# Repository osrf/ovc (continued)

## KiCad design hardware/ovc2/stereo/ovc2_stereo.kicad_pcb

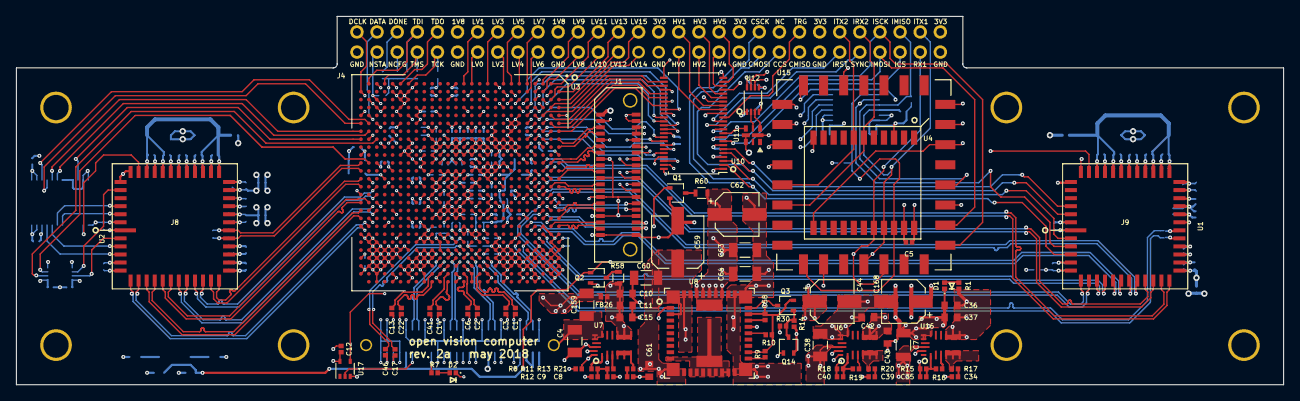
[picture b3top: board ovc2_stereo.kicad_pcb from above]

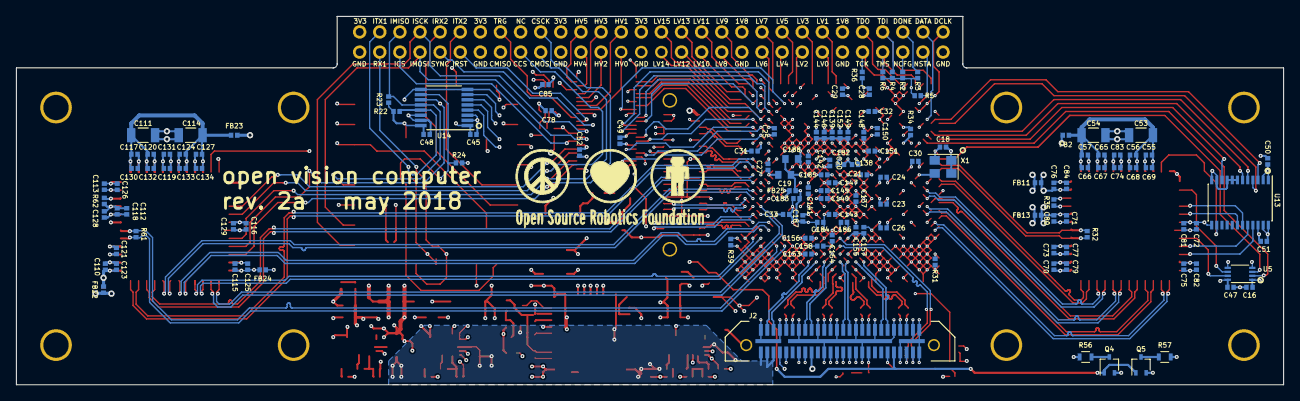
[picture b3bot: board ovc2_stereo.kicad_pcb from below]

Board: 6 copper layers, 160.0 x 46.5 mm, 217 parts (135 on the bottom side), 222 nets.

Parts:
C1, C2, C3, C5, C6, C12, C13, C14, C16, C17, C22, C27, C28, C41, C45, C46, C47, C48, C49, C50, C51, C52, C77, C78, C79, C80, C81, C82, C83, C84, C85, C121, C123, C125, C126, C128, C129, C131, C146, C147, C154, C155, C183, C184: 100n; C_0402_1005Metric
C4, C7, C38, C60: 22u; C_1206_3216Metric
C8, C34, C39: 470p; C_0402_1005Metric
C9, C35, C40: 22p; C_0402_1005Metric
C10, C11, C15, C36, C37, C42, C43: 22u; C_0603_1608Metric
C18, C75, C118, C143: 10n; C_0402_1005Metric
C19, C188: 47u; C_0603_1608Metric
C20, C21, C23, C24, C137, C138, C139, C140, C141, C142, C153, C182: 22n; C_0402_1005Metric
C25, C26, C144, C145: 47n; C_0402_1005Metric
C29, C148, C156, C185: 220n; C_0402_1005Metric
C30, C149, C157, C186: 470n; C_0402_1005Metric
C31, C66, C67, C68, C69, C130, C132, C133, C134, C150, C158, C187: 1u; C_0402_1005Metric
C32, C33, C55, C56, C57, C65, C74, C76, C116, C117, C119, C120, C124, C127, C151, C152: 4u7; C_0402_1005Metric
C44, C62, C168: 220u; CP_Elec_5x5.9
C53, C54, C63, C64, C111, C114, C159: 100u; C_1206_3216Metric
C58: 3n3; C_0402_1005Metric
C59: 100u; CP_Elec_6.3x7.7
C61: 100n; C_0603_1608Metric
C70, C71, C72, C73, C110, C112, C113, C115: 10u; C_0402_1005Metric
D1: LED_Red; LED_0402_1005Metric
D2: LED_Green; LED_0402_1005Metric
FB2, FB11, FB13, FB22, FB23, FB24, FB25, FB26: 60; R_0402_1005Metric
J1: HIGH-SPEED EXPANSION; SAMTEC_ERF8-020
J2: Samtec QRM8; SAMTEC_QRM8-026-02.0-L-D-A-GP
J4: LOW-SPEED EXPANSION; Pin_Header_Straight_2x30_Pitch2.54mm
J8, J9: LENS_HOLDER; LENS_HOLDER_30MM
Q1, Q2, Q3, Q4, Q5, Q14: NTS4001NT1G; SOT-323_SC-70
R1, R7: 330; R_0402_1005Metric
R2, R3, R4, R5, R6, R8, R14, R22, R23, R24, R30: 10k; R_0402_1005Metric
R9: 1M; R_0402_1005Metric
R10: 2k87; R_0402_1005Metric
R11, R12, R15, R18: 51k; R_0402_1005Metric
R13: 71k5; R_0402_1005Metric
R16: 11k3; R_0402_1005Metric
R17, R20, R21: 5R1; R_0402_1005Metric
R19: 25k5; R_0402_1005Metric
R31, R39: 2k; R_0402_1005Metric
R32, R61: 100; R_0402_1005Metric
R34, R36: 1k; R_0402_1005Metric
R35, R62: 47k; R_0402_1005Metric
R56, R57, R58, R60: 47; R_0603
U1, U2: NOIP1SN1300A-QDI; LCC101.6P1422X1422X165-48
U3: 10CXyyy_F672; INTEL_F672
U4: VN-100
U5, U12: SN74LVC2T45; VSSOP-8_2.3x2mm_Pitch0.5mm
U6, U7, U16: MPM3630
U8: LMZ31707; TI_RVQ_42
U10: SN74AVC16T245; TSSOP-48_6.1x12.5mm_Pitch0.5mm
U11: led_dotstar_micro; APA102_2020
U13: SN74AVC8T245; TSSOP-24_4.4x7.8mm_Pitch0.65mm
U14: SN74AVC4T245; TSSOP-16_4.4x5mm_Pitch0.65mm
U15: uIMU-2; DFP-22_0.5mmPitch_125x155mm
U17: 74LVC1G34; SOT-353_SC-70-5
X1: ASEMB-100MHz; Oscillator_SMD_Abracon_ASE-4pin_3.2x2.5mm
Z1: Logo_Open_Hardware_Small; OSHW-Symbol_6.7x6mm_SilkScreen
Z2: Logo_Open_Hardware_Small; OSRF_logo

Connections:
0V9: C62.1, C63.1, C64.1, C137.1, C138.1, C139.1, C140.1, C141.1, C142.1, C143.1, C144.1, C145.1, C146.1, C147.1, C148.1, C149.1, C150.1, C151.1, C152.1, R60.1, U3.K9, U3.K10, U3.K15, U3.K16, U3.K17, U3.L8, U3.L9, U3.L13, U3.L14, U3.L17, U3.L18, U3.M8, U3.M9, U3.M10, U3.M13, U3.M14, U3.M15, U3.M16, U3.N8, U3.N10, U3.N12, U3.N15, U3.N16, U3.N17, U3.N18, U3.P8, U3.P9, U3.P10, U3.P12, U3.P13, U3.P14, U3.P15, U3.P17, U3.P18, U3.R9, U3.R12, U3.R14, U3.R15, U3.R16, U3.R17, U3.T8, U3.T9, U3.T12, U3.T13, U3.T14, U3.T17, U3.T18, U3.U8, U3.U9, U3.U10, U3.U11, U3.U13, U3.U14, U3.U15, U3.U16, U3.U18, U8.27, U8.34, U8.35, U8.36, U8.37, U8.38, U8.41
1V03: C9.1, C10.1, C11.1, C15.1, FB26.2, R12.1, R58.1, U7.7, U7.8, U7.9
+1V8: C12.1, C16.1, C18.1, C20.1, C21.1, C23.1, C24.1, C25.1, C26.1, C27.1, C28.1, C29.1, C30.1, C31.1, C32.1, C33.1, C40.1, C42.1, C43.1, C44.1, C45.1, C49.1, C50.1, C85.1, FB13.2, FB24.2, FB25.2, J1.6, J1.8, J4.12, J4.22, R2.1, R3.1, R4.1, R5.1, R6.1, R18.1, R34.1, R57.1, U3.AA15, U3.AB12, U3.AB17, U3.C9, U3.D11, U3.D16, U3.E8, U3.E18, U3.F15, U3.L11, U3.L16, U3.R3, U3.T5, U3.T11, U3.T16, U3.U2, U3.V10, U3.V11, U3.V12, U3.W16, U3.Y13, U3.Y18, U5.1, U6.7, U6.8, U6.9, U10.1, U10.24, U10.31, U10.42, U12.8, U13.1, U13.2, U14.1, U17.5, X1.1, X1.4
+3V3: C5.1, C35.1, C36.1, C37.1, C47.1, C48.1, C51.1, C52.1, C168.1, FB2.2, FB11.2, FB22.2, FB23.2, J1.2, J1.4, J4.32, J4.40, J4.48, J4.60, R1.2, R15.1, R22.1, R23.1, R24.1, R56.1, U4.10, U5.8, U10.7, U10.18, U13.23, U13.24, U14.16, U15.3, U15.22, U16.7, U16.8, U16.9
+5V: C78.1, J1.1, J2.18, U11.1, U12.1
+12V: C4.1, C7.1, C38.1, C59.1, C60.1, C61.1, J2.2, J2.4, J2.6, R30.1, U6.16, U7.16, U8.1, U8.3, U8.11, U8.12, U8.39, U8.40, U16.16
/fpga_io/CAM1_CS_1V8: U3.D7, U10.44
/fpga_io/CAM1_MISO_1V8: U3.G3, U14.6
/fpga_io/CAM1_MOSI_1V8: U3.D8, U10.46
/fpga_io/CAM1_RST_1V8: U3.C7, U10.43
/fpga_io/CAM1_SCK_1V8: U3.E9, U10.47
/fpga_io/CAM1_TRG_1V8: U3.D4, U10.35
/fpga_io/CAM2_CS_1V8: U3.AE7, U13.6
/fpga_io/CAM2_MISO_1V8: U3.AD8, U5.2
/fpga_io/CAM2_MONITOR_1V8: U3.AE11, U5.3
/fpga_io/CAM2_MOSI_1V8: U3.AF6, U13.4
/fpga_io/CAM2_RST_1V8: U3.AF7, U13.5
/fpga_io/CAM2_SCK_1V8: U3.AE6, U13.3
/fpga_io/CAM2_TRG_1V8: U3.AF8, U13.10
/fpga_io/CLK100: U3.AC13, X1.3
/fpga_io/HSEXP8: J1.26, U3.D15
/fpga_io/HSEXP9: J1.24, U3.E15
/fpga_io/HSEXP10: J1.22, U3.D13
/fpga_io/HSEXP11: J1.20, U3.E14
/fpga_io/HSEXP12: J1.18, U3.D12
/fpga_io/HSEXP13: J1.16, U3.D14
/fpga_io/HSEXP14: J1.14, U3.E11
/fpga_io/HSEXP15: J1.12, U3.D10
/fpga_io/HSEXP16: J1.10, U3.C8
/fpga_io/HSEXP_0+: J1.37, U3.A19
/fpga_io/HSEXP_0-: J1.35, U3.B19
/fpga_io/HSEXP_1+: J1.38, U3.B18
/fpga_io/HSEXP_1-: J1.36, U3.C18
/fpga_io/HSEXP_2+: J1.31, U3.A18
/fpga_io/HSEXP_2-: J1.29, U3.A17
/fpga_io/HSEXP_3+: J1.32, U3.A16
/fpga_io/HSEXP_3-: J1.30, U3.B16
/fpga_io/HSEXP_4+: J1.25, U3.A14
/fpga_io/HSEXP_4-: J1.23, U3.B14
/fpga_io/HSEXP_5+: J1.17, U3.A12
/fpga_io/HSEXP_5-: J1.19, U3.A13
/fpga_io/HSEXP_6+: J1.13, U3.A11
/fpga_io/HSEXP_6-: J1.11, U3.B11
/fpga_io/HSEXP_7+: J1.7, U3.A9
/fpga_io/HSEXP_7-: J1.5, U3.A8
/fpga_io/IMU_CS_1V8: U3.C6, U10.41
/fpga_io/IMU_MISO_1V8: U3.F4, U14.5
/fpga_io/IMU_MOSI_1V8: U3.D5, U10.40
/fpga_io/IMU_NRST_1V8: U3.C3, U10.36
/fpga_io/IMU_SCK_1V8: U3.E5, U10.38
/fpga_io/IMU_SYNC_IN_1V8: U3.E4, U10.37
/fpga_io/IMU_SYNC_OUT_1V8: U3.H2, U14.7
/fpga_io/IMU_TX1_1V8: U3.E6, U14.4
/fpga_io/LED_CI_1V8: U3.D3, U12.6
/fpga_io/LED_CI_5V: U11.5, U12.2
/fpga_io/LED_DI_1V8: U3.D2, U12.7
/fpga_io/LED_DI_5V: U11.4, U12.3
/fpga_io/LSEXP_0: J4.13, U3.M1
/fpga_io/LSEXP_1: J4.14, U3.N1
/fpga_io/LSEXP_2: J4.15, U3.H1
/fpga_io/LSEXP_3: J4.16, U3.K1
/fpga_io/LSEXP_4: J4.17, U3.F1
/fpga_io/LSEXP_5: J4.18, U3.G1
/fpga_io/LSEXP_6: J4.19, U3.E2
/fpga_io/LSEXP_7: J4.20, U3.E1
/fpga_io/LSEXP_8: J4.23, U3.C2
/fpga_io/LSEXP_9: J4.24, U3.C1
/fpga_io/LSEXP_10: J4.25, U3.B3
/fpga_io/LSEXP_11: J4.26, U3.B1
/fpga_io/LSEXP_12: J4.27, U3.A3
/fpga_io/LSEXP_13: J4.28, U3.A2
/fpga_io/LSEXP_14: J4.29, U3.A4
/fpga_io/LSEXP_15: J4.30, U3.B4
/fpga_io/LSEXP_HV_0: J4.33, U10.16
/fpga_io/LSEXP_HV_0_1V8: U3.F3, U10.33
/fpga_io/LSEXP_HV_1: J4.34, U10.17
/fpga_io/LSEXP_HV_1_1V8: U3.A7, U10.32
/fpga_io/LSEXP_HV_2: J4.35, U10.19
/fpga_io/LSEXP_HV_2_1V8: U3.B6, U10.30
/fpga_io/LSEXP_HV_3: J4.36, U10.20
/fpga_io/LSEXP_HV_3_1V8: U3.A6, U10.29
/fpga_io/LSEXP_HV_4: J4.37, U10.22
/fpga_io/LSEXP_HV_4_1V8: U3.B5, U10.27
/fpga_io/LSEXP_HV_5: J4.38, U10.23
/fpga_io/LSEXP_HV_5_1V8: U3.C5, U10.26
/fpga_io/PCIE_RST_1V8: U3.AB8, U17.4
/fpga_pcie/GXB_TX_L0+: C22.2, U3.U26
/fpga_pcie/GXB_TX_L0-: C13.2, U3.U25
/fpga_pcie/GXB_TX_L1+: C14.2, U3.R26
/fpga_pcie/GXB_TX_L1-: C41.2, U3.R25
/fpga_pcie/GXB_TX_L2+: C6.2, U3.N26
/fpga_pcie/GXB_TX_L2-: C2.2, U3.N25
/fpga_pcie/GXB_TX_L3+: C1.2, U3.L26
/fpga_pcie/GXB_TX_L3-: C3.2, U3.L25
/fpga_pcie/REFCLK+: C17.2, U3.N22
/fpga_pcie/REFCLK-: C46.2, U3.N21
/fpga_power/RREF_BL: R31.1, U3.AF23
/fpga_power/RREF_TL: R39.1, U3.A21
/fpga_power/VCCA: C19.1, C182.1, C183.1, C184.1, C185.1, C186.1, C187.1, C188.1, FB25.1, U3.K20, U3.N11, U3.N13, U3.P20
/fpga_power/VCC_GXBL: C153.1, C154.1, C155.1, C156.1, C157.1, C158.1, C159.1, FB26.1, U3.K21, U3.K22, U3.M21, U3.M22, U3.P21, U3.P22, U3.T21, U3.T22
/imagers/CAM1_1V8: C112.1, C115.1, C118.1, C121.1, C125.1, C128.1, FB24.1, U1.6, U1.22, U1.26
/imagers/CAM1_3V3: C110.1, C113.1, C116.1, C119.1, C123.1, C126.1, C129.1, C131.1, FB22.1, U1.1, U1.19, U1.29, U1.36
/imagers/CAM1_VDDPIX: C111.1, C114.1, C117.1, C120.1, C124.1, C127.1, C130.1, C132.1, C133.1, C134.1, FB23.1, U1.31, U1.33, U1.38, U1.40
/imagers/CAM2_1V8: C71.1, C73.1, C75.1, C77.1, C80.1, C82.1, FB13.1, U2.6, U2.22, U2.26
/imagers/CAM2_3V3: C70.1, C72.1, C74.1, C76.1, C79.1, C81.1, C83.1, C84.1, FB11.1, U2.1, U2.19, U2.29, U2.36
/imagers/CAM2_VDDPIX: C53.1, C54.1, C55.1, C56.1, C57.1, C65.1, C66.1, C67.1, C68.1, C69.1, FB2.1, U2.31, U2.33, U2.38, U2.40
/power/AGND: C58.2, Q3.2, R9.2, R10.2, U8.2, U8.23, U8.29
/power/PG_GRP1: R8.2, U6.17, U7.18, U16.17
/power/PH: U8.10, U8.13, U8.14, U8.15, U8.16, U8.17, U8.18, U8.19, U8.42
/power/~PWR_EN_GRP1: Q3.1, Q14.3, R14.1, R30.2
CAM1_CLKIN+: R61.1, U1.23, U3.F21
CAM1_CLKIN-: R61.2, U1.24, U3.E21
CAM1_CLKOUT+: U1.7, U3.C17
CAM1_CLKOUT-: U1.8, U3.C16
CAM1_CS_3V3: J4.43, U1.47, U10.5
CAM1_DOUT0+: U1.9, U3.C21
CAM1_DOUT0-: U1.10, U3.C20
CAM1_DOUT1+: U1.11, U3.D19
CAM1_DOUT1-: U1.12, U3.E19
CAM1_DOUT2+: U1.13, U3.B15
CAM1_DOUT2-: U1.14, U3.C15
CAM1_DOUT3+: U1.15, U3.B13
CAM1_DOUT3-: U1.16, U3.C13
CAM1_MISO_3V3: J4.45, U1.3, U14.11
CAM1_MOSI_3V3: J4.41, U1.2, U10.3
CAM1_RST_3V3: U1.46, U10.6
CAM1_SCK_3V3: J4.42, U1.4, U10.2
CAM1_SYNC+: U1.17, U3.C11
CAM1_SYNC-: U1.18, U3.C12
CAM1_TRG_3V3: J4.46, U1.41, U10.14
CAM2_CLKIN+: R32.2, U2.24, U3.AF11
CAM2_CLKIN-: R32.1, U2.23, U3.AF12
CAM2_CLKOUT+: U2.7, U3.AF19
CAM2_CLKOUT-: U2.8, U3.AE19
CAM2_CS_3V3: U2.47, U13.18
CAM2_DOUT0+: U2.9, U3.AF18
CAM2_DOUT0-: U2.10, U3.AF17
CAM2_DOUT1+: U2.11, U3.AF16
CAM2_DOUT1-: U2.12, U3.AE16
CAM2_DOUT2+: U2.13, U3.AD17
CAM2_DOUT2-: U2.14, U3.AE17
CAM2_DOUT3+: U2.15, U3.AD15
CAM2_DOUT3-: U2.16, U3.AD14
CAM2_MISO_3V3: U2.2, U5.7
CAM2_MONITOR: U2.44, U5.6
CAM2_MOSI_3V3: U2.3, U13.20
CAM2_RST_3V3: U2.46, U13.19
CAM2_SCK_3V3: U2.4, U13.21
CAM2_SYNC+: U2.18, U3.AF13
CAM2_SYNC-: U2.17, U3.AF14
CAM2_TRG_3V3: U2.41, U13.14
DISCHARGE: J2.44, Q1.1, Q2.1, Q4.1, Q5.1
FPGA_CONFIG_DATA0: J2.30, J4.4, U3.AE5
FPGA_CONFIG_DCLK: J2.32, J4.2, U3.AF2
FPGA_CONF_DONE: J2.28, J4.6, R3.2, U3.AB1
FPGA_NCONFIG: J2.24, J4.5, R2.2, U3.Y5
FPGA_NSTATUS: J2.26, J4.3, R5.2, U3.AD3
FPGA_TCK: J4.9, R36.1, U3.Y1
FPGA_TDI: J4.8, R4.2, U3.AE1
FPGA_TDO: J4.10, U3.AA1
FPGA_TMS: J4.7, R6.2, U3.AC1
GND: C4.2, C5.2, C7.2, C8.2, C10.2, C11.2, C12.2, C15.2, C16.2, C18.2, C19.2, C20.2, C21.2, C23.2, C24.2, C25.2, C26.2, C27.2, C28.2, C29.2, C30.2, C31.2, C32.2, C33.2, C34.2, C36.2, C37.2, C38.2, C39.2, C42.2, C43.2, C44.2, C45.2, C47.2, C48.2, C49.2, C50.2, C51.2, C52.2, C53.2, C54.2, C55.2, C56.2, C57.2, C59.2, C60.2, C61.2, C62.2, C63.2, C64.2, C65.2, C66.2, C67.2, C68.2, C69.2, C70.2, C71.2, C72.2, C73.2, C74.2, C75.2, C76.2, C77.2, C78.2, C79.2, C80.2, C81.2, C82.2, C83.2, C84.2, C85.2, C110.2, C111.2, C112.2, C113.2, C114.2, C115.2, C116.2, C117.2, C118.2, C119.2, C120.2, C121.2, C123.2, C124.2, C125.2, C126.2, C127.2, C128.2, C129.2, C130.2, C131.2, C132.2, C133.2, C134.2, C137.2, C138.2, C139.2, C140.2, C141.2, C142.2, C143.2, C144.2, C145.2, C146.2, C147.2, C148.2, C149.2, C150.2, C151.2, C152.2, C153.2, C154.2, C155.2, C156.2, C157.2, C158.2, C159.2, C168.2, C182.2, C183.2, C184.2, C185.2, C186.2, C187.2, C188.2, D1.1, D2.1, J1.3, J1.9, J1.15, J1.21, J1.27, J1.28, J1.33, J1.34, J1.39, J1.40, J2.1, J2.7, J2.13, J2.19, J2.22, J2.25, J2.31, J2.34, J2.37, J2.43, J2.46, J2.49, J2.51, J2.52, J2.53, J2.54, J2.55, J2.56, J4.1, J4.11, J4.21, J4.31, J4.39, J4.47, J4.59, J8.1, J9.1, Q1.2, Q2.2, Q4.2, Q5.2, Q14.2, R14.2, R31.2, R35.2, R36.2, R39.2, R62.2, U1.5, U1.20, U1.21, U1.25, U1.27, U1.30, U1.32, U1.34, U1.35, U1.37, U1.39, U1.42, U1.43, U1.48, U2.5, U2.20, U2.21, U2.25, U2.27, U2.30, U2.32, U2.34, U2.35, U2.37, U2.39, U2.42, U2.43, U2.48, U3.A5, U3.A10, U3.A15, U3.A20, U3.A22, U3.A23, U3.A24, U3.A25, U3.AA2, U3.AA3, U3.AA4, U3.AA5, U3.AA10, U3.AA20, U3.AA22, U3.AA23, U3.AA24, U3.AB2, U3.AB7, U3.AB22, U3.AB23, U3.AB24, U3.AB25, U3.AB26, U3.AC4, U3.AC9, U3.AC14, U3.AC19, U3.AC22, U3.AC23, U3.AC24, U3.AD1, U3.AD4, U3.AD6, U3.AD11, U3.AD16, U3.AD21, U3.AD22, U3.AD23, U3.AD24, U3.AD25, U3.AD26, U3.AE3, U3.AE8, U3.AE13, U3.AE18, U3.AE20, U3.AE21, U3.AE22, U3.AE23, U3.AE24, U3.AF5, U3.AF10, U3.AF15, U3.AF20, U3.AF24, U3.AF25, U3.B2, U3.B7, U3.B12, U3.B17, U3.B20, U3.B21, U3.B22, U3.B23, U3.B24, U3.B25, U3.B26, U3.C4, U3.C14, U3.C19, U3.C22, U3.C23, U3.C24, U3.D1, U3.D6, U3.D21, U3.D22, U3.D23, U3.D24, U3.D25, U3.D26, U3.E3, U3.E12, U3.E13, U3.E22, U3.E23, U3.E24, U3.F5, U3.F6, U3.F9, U3.F10, U3.F20, U3.F22, U3.F23, U3.F24, U3.F25, U3.F26, U3.G2, U3.G6, U3.G7, U3.G8, U3.G9, U3.G12, U3.G17, U3.G21, U3.G22, U3.G23, U3.G24, U3.H4, U3.H8, U3.H9, U3.H11, U3.H14, U3.H17, U3.H19, U3.H22, U3.H23, U3.H24, U3.H25, U3.H26, U3.J1, U3.J6, U3.J7, U3.J8, U3.J9, U3.J10, U3.J11, U3.J12, U3.J16, U3.J20, U3.J21, U3.J22, U3.J23, U3.J24, U3.K3, U3.K8, U3.K11, U3.K12, U3.K13, U3.K18, U3.K25, U3.K26, U3.L5, U3.L10, U3.L12, U3.L15, U3.L20, U3.L21, U3.L22, U3.L23, U3.L24, U3.M2, U3.M7, U3.M11, U3.M12, U3.M17, U3.M20, U3.M25, U3.M26, U3.N4, U3.N9, U3.N14, U3.N19, U3.N20, U3.N23, U3.N24, U3.P1, U3.P6, U3.P11, U3.P16, U3.P25, U3.P26, U3.R6, U3.R8, U3.R13, U3.R18, U3.R20, U3.R21, U3.R22, U3.R23, U3.R24, U3.T10, U3.T15, U3.T20, U3.T25, U3.T26, U3.U7, U3.U12, U3.U17, U3.U20, U3.U21, U3.U22, U3.U23, U3.U24, U3.V4, U3.V9, U3.V14, U3.V15, U3.V17, U3.V19, U3.V20, U3.V21, U3.V22, U3.V23, U3.V24, U3.V25, U3.V26, U3.W1, U3.W4, U3.W5, U3.W6, U3.W11, U3.W21, U3.W22, U3.W23, U3.W24, U3.Y2, U3.Y3, U3.Y8, U3.Y9, U3.Y10, U3.Y22, U3.Y23, U3.Y24, U3.Y25, U3.Y26, U4.1, U4.2, U4.3, U4.4, U4.18, U4.28, U4.30, U5.4, U5.5, U6.12, U6.13, U6.14, U7.12, U7.13, U7.14, U8.20, U8.21, U8.31, U8.32, U8.33, U10.4, U10.10, U10.15, U10.21, U10.25, U10.28, U10.34, U10.39, U10.45, U10.48, U11.6, U12.4, U12.5, U13.7, U13.8, U13.9, U13.11, U13.12, U13.13, U13.22, U14.2, U14.3, U14.8, U14.9, U14.14, U14.15, U15.11, U15.21, U16.12, U16.13, U16.14, U17.3, X1.2
IMU_CS_3V3: J4.55, U4.23, U10.8
IMU_MISO_3V3: J4.56, R23.2, U4.19, U14.12
IMU_MOSI_3V3: J4.53, U4.17, U10.9
IMU_NRST_3V3: J4.49, U4.21, U10.13, U15.12
IMU_RX1_3V3: J2.16, J4.57, U4.13, U15.18
IMU_RX2_3V3: J4.52, U4.6, U15.6
IMU_SCK_3V3: J4.54, U4.16, U10.11
IMU_SYNC_IN_3V3: J4.51, U4.22, U10.12
IMU_SYNC_OUT_3V3: R24.2, U4.9, U14.10, U15.20
IMU_TX1_3V3: J2.14, J4.58, R22.2, U4.12, U14.13, U15.19
IMU_TX2_3V3: J4.50, U4.5, U15.7
JETSON_CARRIER_PWR_ON: J2.8, Q14.1, U7.17
JETSON_RESET_OUT: J2.10, U6.18
unnamed: C8.1, R21.2
unnamed: C9.2, R11.1, R12.2, R13.1
unnamed: C34.1, R17.2
unnamed: C35.2, R15.2, R16.1, U16.1
unnamed: C39.1, R20.2
unnamed: C40.2, R18.2, R19.1, U6.1
unnamed: C58.1, U8.28
unnamed: D1.2, R1.1
unnamed: D2.2, R7.1
unnamed: Q1.3, R60.2
unnamed: Q2.3, R58.2
unnamed: Q3.3, U8.30
unnamed: Q4.3, R56.2
unnamed: Q5.3, R57.2
unnamed: R8.1, U7.2
unnamed: R9.1, U8.22
unnamed: R10.1, U8.26
unnamed: R11.2, U7.1
unnamed: R13.2, U7.3
unnamed: R16.2, U16.3
unnamed: R17.1, U16.4, U16.5, U16.6
unnamed: R19.2, U6.3
unnamed: R20.1, U6.4, U6.5, U6.6
unnamed: R21.1, U7.4, U7.5, U7.6
unnamed: R34.2, U3.AA6
unnamed: R35.1, U2.28
unnamed: R62.1, U1.28
PCIE_LANE0_RX+: J2.39, U3.T24
PCIE_LANE0_RX-: J2.41, U3.T23
PCIE_LANE0_TX+: C22.1, J2.45
PCIE_LANE0_TX-: C13.1, J2.47
PCIE_LANE1_RX+: J2.27, U3.P24
PCIE_LANE1_RX-: J2.29, U3.P23
PCIE_LANE1_TX+: C14.1, J2.33
PCIE_LANE1_TX-: C41.1, J2.35
PCIE_LANE2_RX+: J2.17, U3.M24
PCIE_LANE2_RX-: J2.15, U3.M23
PCIE_LANE2_TX+: C6.1, J2.23
PCIE_LANE2_TX-: C2.1, J2.21
PCIE_LANE3_RX+: J2.5, U3.K24
PCIE_LANE3_RX-: J2.3, U3.K23
PCIE_LANE3_TX+: C1.1, J2.9
PCIE_LANE3_TX-: C3.1, J2.11
PCIE_REFCLK+: C17.1, J2.48
PCIE_REFCLK-: C46.1, J2.50
PCIE_RST_3V3: J2.42, U17.2
TX2_LED: J2.36, R7.2

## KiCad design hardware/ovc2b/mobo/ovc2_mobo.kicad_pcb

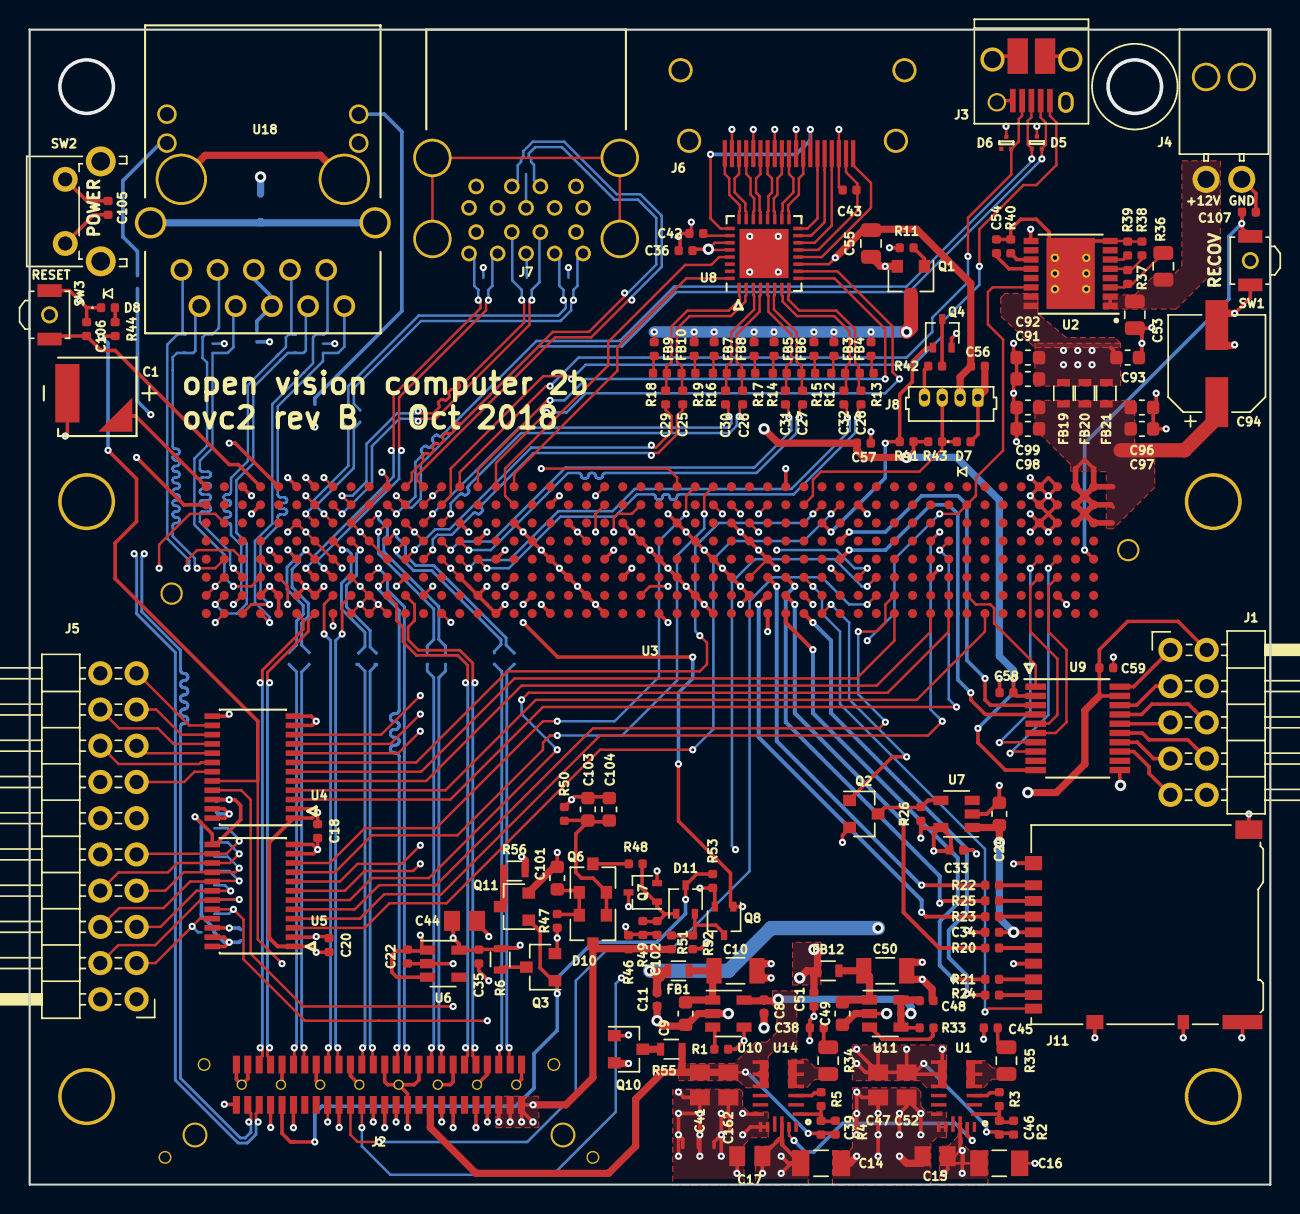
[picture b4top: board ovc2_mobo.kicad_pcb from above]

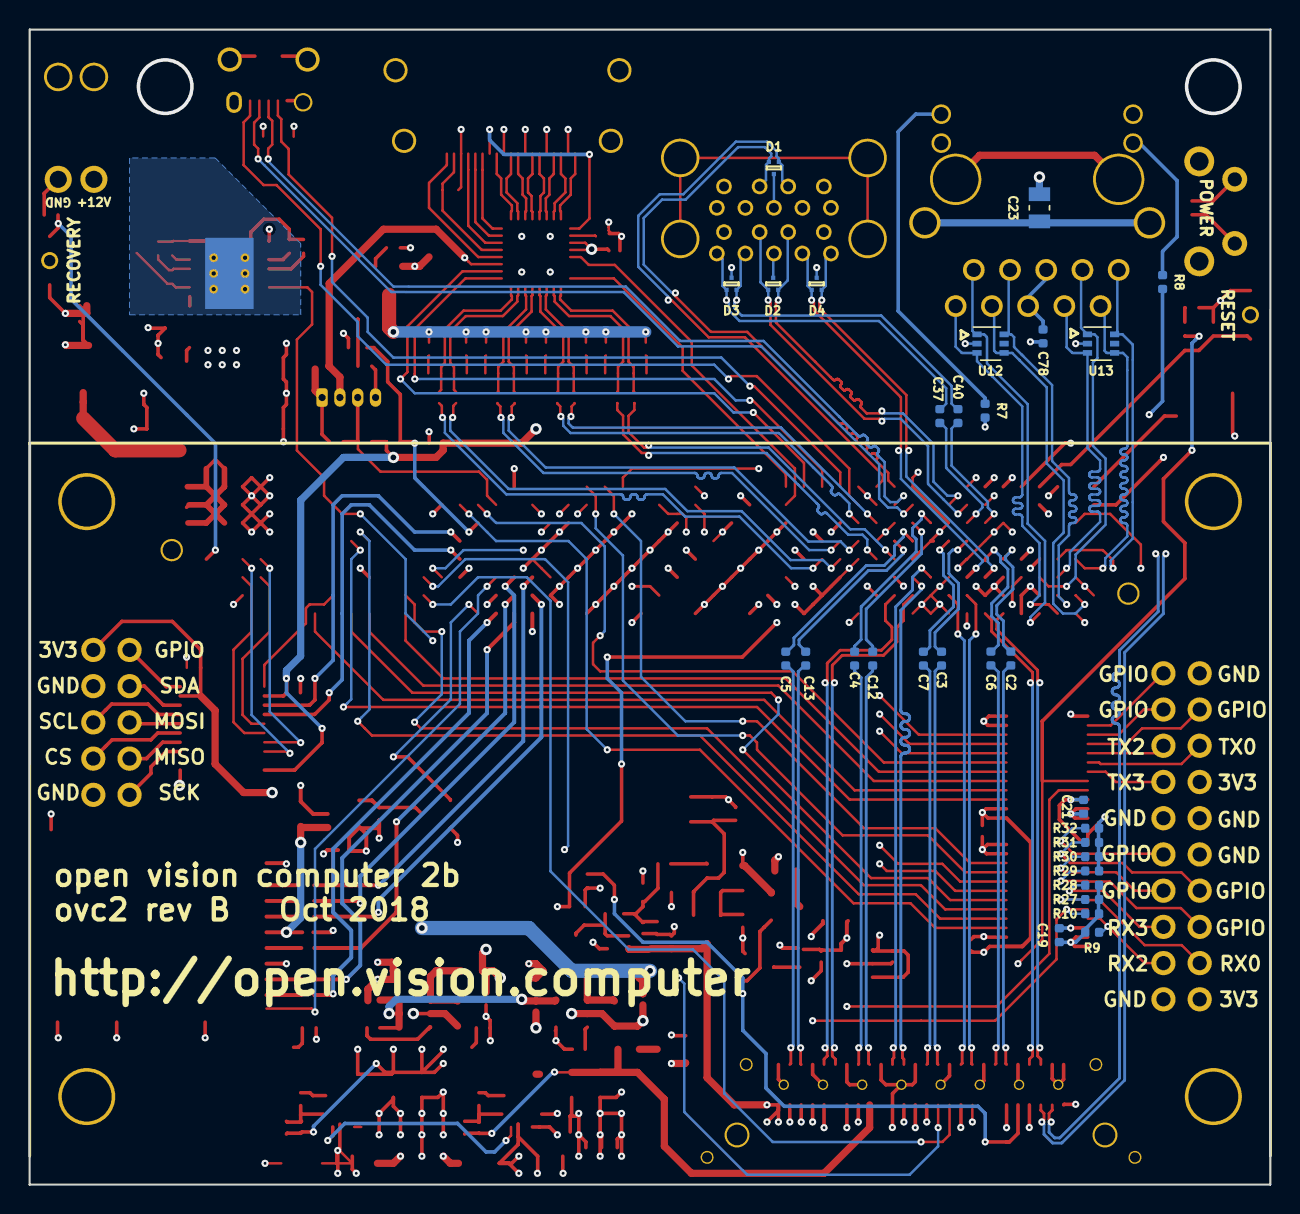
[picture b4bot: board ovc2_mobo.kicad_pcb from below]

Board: 6 copper layers, 87.0 x 81.0 mm, 189 parts (30 on the bottom side), 216 nets.

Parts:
C1: 80m; SEIKO_XH414HG_IV01E
C2, C3, C4, C5, C6, C7, C8, C11, C12, C13, C18, C19, C20, C21, C25, C26, C27, C28, C29, C30, C31, C32, C34, C36, C37, C40, C42, C48, C51, C56, C57, C58, C59, C105, C106, C107: 100n; C_0402_1005Metric
C9, C24, C49, C91, C92, C93, C96, C97, C98, C99, C103, C104: 10u; C_0603_1608Metric
C10, C50: 68u; C_1206_3216Metric
C14, C16: 33u; C_1206_3216Metric
C15, C17, C41, C44, C47, C52, C55, C162: 22u; C_0805_2012Metric
C22, C33, C35, C43, C102: 1u; C_0402_1005Metric
C23: 100p; C_0805_2012Metric
C38, C45: 470p; C_0402_1005Metric
C39, C46: 22p; C_0402_1005Metric
C53: 1u; C_0805_2012Metric
C54: 47n; C_0402_1005Metric
C78: 10n; C_0402_1005Metric
C94: 100u; CP_Elec_6.3x7.7
C101: 2u2; C_0603_1608Metric
D1, D2, D3, D4, D5, D6: TPD2EUSB30A; TPD2EUSB30x
D7: ESD9X5.0ST5G; D_0402_1005Metric
D8: LED_Small; D_0402_1005Metric
D10: BAT54ALT1G; SOT-23
D11: BAT54CW-7-F; SOT-323_SC-70
FB1, FB12: 220; R_0603
FB3, FB4, FB5, FB6, FB7, FB8, FB9, FB10: 600; R_0402_1005Metric
FB19, FB20, FB21: 30; R_0603
J1: SPI/I2C; Pin_Header_Angled_2x05_Pitch2.54mm
J2: SAMTEC QRF8-RA; SAMTEC_QRF8-026-01-L-RA-GP
J3: USB_OTG; USB_Micro-B_10103594-0001LF
J4: POWER; Molex_NanoFit_1x02x2.50mm_Angled
J5: GPIO; Pin_Header_Angled_2x10_Pitch2.54mm
J6: HDMI_TYPE_A; AMP_FCI_10029449-111RLF_HDMI_TYPE_A
J7: USB; MOLEX_0484060003
J8: FAN; Molex_PicoBlade_53047-0810_1x04_P1.25mm_Vertical
J11: Micro_SD_Card_Det_Hirose_DM3AT; Hirose_DM3AT-SF-PEJM5
Q1: Q_NMOS_GSD; SOT-23
Q2: DMN2041L; SOT-23
Q3, Q10, Q11: NTR4003NT1G; SOT-23
Q4, Q7, Q8: NTS4001NT1G; SOT-323_SC-70
Q6: MMBT4403; SOT-23
R1, R9, R10, R11, R27, R28, R29, R30, R31, R32, R33, R41, R46, R47, R48: 10k; R_0402_1005Metric
R2, R4: 51k; R_0402_1005Metric
R3: 11k3; R_0402_1005Metric
R5: 6k98; R_0402_1005Metric
R6, R56: 47; R_0603
R7, R8: 681; R_0402_1005Metric
R12, R13, R14, R15, R16, R17, R18, R19: 499; R_0402_1005Metric
R20: 0; R_0402_1005Metric
R21, R22, R23, R24, R25: 10; R_0402_1005Metric
R26, R38, R51: 47k; R_0402_1005Metric
R34, R35: 4R99; R_0805_2012Metric
R36: 487k; R_0805_2012Metric
R37: 18k9; R_0402_1005Metric
R39: 402k; R_0402_1005Metric
R40: 5k6; R_0402_1005Metric
R42: 100; R_0402_1005Metric
R43, R49, R52, R53: 100k; R_0402_1005Metric
R44: 330; R_0402_1005Metric
R50: 10M; R_0402_1005Metric
R55: 100; R_0603
SW1, SW3: SW_Push; SW_SPST_B3U-3000P-B
SW2: SW_Push; SW_Tactile_SPST_Angled_PTS645Vx58-2LFS
U1, U14: MPM3630
U2: TPS26600PWP; HTSSOP-16-1EP_4.4x5mm_P0.65mm_EP3.4x5mm_Mask3x3mm_ThermalVi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
U3: Jetson; JETSON_TX
U4, U5: SN74AVC8T245; TSSOP-24_4.4x7.8mm_Pitch0.65mm
U6: TLV733P; SOT-23-5
U7: NCP380LSN10AAT1G; SOT-23-5
U8: IP4786CZ32; QFN-32-1EP_5x5mm_Pitch0.5mm
U9: TXS0108EPW; TSSOP-20_4.4x6.5mm_P0.65mm
U10, U11: TPS2069C; SOT-23-5
U12, U13: SP3002-04JTG; SOT-363_SC-70-6
U18: ARJ11C-MBSAS-A-BA-7MU2

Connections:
+1V8: C18.1, C20.1, C35.2, C36.1, C44.1, C57.1, C58.2, R6.1, R41.1, R43.1, U4.1, U4.2, U5.1, U6.5, U8.27, U8.28, U9.2, U9.10
+3V3: C19.1, C21.1, C22.2, C33.1, C46.1, C47.1, C52.1, C59.2, J1.2, J5.2, J5.14, R2.1, R9.1, R10.1, R11.1, R26.1, R27.1, R28.1, R56.1, U1.7, U1.8, U1.9, U4.23, U4.24, U5.23, U5.24, U6.1, U6.3, U7.5, U9.19, U18.12, U18.13
+5V: C8.1, C39.1, C41.1, C48.1, C55.1, C56.1, C162.1, J2.18, J8.2, R4.1, R33.1, R55.1, U8.11, U10.5, U11.4, U11.5, U14.7, U14.8, U14.9
+12V: C14.1, C15.1, C16.1, C17.1, C91.1, C92.1, C93.1, D10.3, FB19.2, FB20.2, FB21.2, J2.2, J2.4, J2.6, R46.1, R51.1, U1.16, U2.15, U2.16, U14.16
/jetson_enet/GBE_MDI0+: U3.E48, U13.6, U18.1
/jetson_enet/GBE_MDI0-: U3.E49, U13.4, U18.2
/jetson_enet/GBE_MDI1+: U3.F47, U13.1, U18.3
/jetson_enet/GBE_MDI1-: U3.F48, U13.3, U18.4
/jetson_enet/GBE_MDI2+: U3.G48, U12.6, U18.7
/jetson_enet/GBE_MDI2-: U3.G49, U12.4, U18.8
/jetson_enet/GBE_MDI3+: U3.H47, U12.1, U18.9
/jetson_enet/GBE_MDI3-: U3.H48, U12.3, U18.10
/jetson_enet/LINK_1G: R8.1, U18.11
/jetson_enet/LINK_ACT: R7.1, U18.14
/jetson_hdmi/CEC: U3.B33, U8.29
/jetson_hdmi/CEC_CON: J6.13, U8.25
/jetson_hdmi/DDC_CLK: U3.A35, U8.9
/jetson_hdmi/DDC_CLK_CON: J6.15, U8.15
/jetson_hdmi/DDC_DAT: U3.A34, U8.10
/jetson_hdmi/DDC_DAT_CON: J6.16, U8.14
/jetson_hdmi/ESD_BYP: C42.1, U8.26
/jetson_hdmi/HDMI_TXC+: C32.2, U3.E36
/jetson_hdmi/HDMI_TXC-: C28.2, U3.E35
/jetson_hdmi/HDMI_TXD0+: C31.2, U3.D37
/jetson_hdmi/HDMI_TXD0-: C27.2, U3.D36
/jetson_hdmi/HDMI_TXD1+: C30.2, U3.C38
/jetson_hdmi/HDMI_TXD1-: C26.2, U3.C37
/jetson_hdmi/HDMI_TXD2+: C29.2, U3.E39
/jetson_hdmi/HDMI_TXD2-: C25.2, U3.E38
/jetson_hdmi/HPD: U3.A33, U8.32
/jetson_hdmi/HPDET_CON: J6.19, U8.12
/jetson_hdmi/TMDS_CON_CK+: J6.10, U8.18
/jetson_hdmi/TMDS_CON_CK-: J6.12, U8.17
/jetson_hdmi/TMDS_CON_D0+: J6.7, U8.20
/jetson_hdmi/TMDS_CON_D0-: J6.9, U8.19
/jetson_hdmi/TMDS_CON_D1+: J6.4, U8.22
/jetson_hdmi/TMDS_CON_D1-: J6.6, U8.21
/jetson_hdmi/TMDS_CON_D2+: J6.1, U8.24
/jetson_hdmi/TMDS_CON_D2-: J6.3, U8.23
/jetson_hdmi/TMDS_SYS_CK+: C32.1, R12.1, U8.7
/jetson_hdmi/TMDS_SYS_CK-: C28.1, R13.1, U8.8
/jetson_hdmi/TMDS_SYS_D0+: C31.1, R14.1, U8.5
/jetson_hdmi/TMDS_SYS_D0-: C27.1, R15.1, U8.6
/jetson_hdmi/TMDS_SYS_D1+: C30.1, R16.1, U8.3
/jetson_hdmi/TMDS_SYS_D1-: C26.1, R17.1, U8.4
/jetson_hdmi/TMDS_SYS_D2+: C29.1, R18.1, U8.1
/jetson_hdmi/TMDS_SYS_D2-: C25.1, R19.1, U8.2
/jetson_hdmi/UTILTY_CON: J6.14, U8.16
/jetson_pcie/PEX0_TX+: C6.2, U3.E44
/jetson_pcie/PEX0_TX-: C2.2, U3.E45
/jetson_pcie/PEX1_TX+: C7.2, U3.D42
/jetson_pcie/PEX1_TX-: C3.2, U3.D43
/jetson_pcie/PEX2_TX+: C12.2, U3.C40
/jetson_pcie/PEX2_TX-: C4.2, U3.C41
/jetson_pcie/PEX3_TX+: C13.2, U3.D39
/jetson_pcie/PEX3_TX-: C5.2, U3.D40
/jetson_power/FAN_PWM: Q4.1, R41.2, U3.C16
/jetson_power/FAN_TACH: D7.1, J8.3, R43.2, U3.B17
/jetson_power/POWER_BTN: C105.1, SW2.1, U3.B50
/jetson_power/RESET_IN: C106.1, SW3.1, U3.A47
/jetson_power/VDD_RTC: C1.1, U3.A50
/jetson_sdcard/SDCARD_CD: J11.9, U3.F17
/jetson_sdcard/SDCARD_CLK: J11.5, R20.1
/jetson_sdcard/SDCARD_CMD: J11.3, R23.1
/jetson_sdcard/SDCARD_D0: J11.7, R21.1
/jetson_sdcard/SDCARD_D1: J11.8, R24.1
/jetson_sdcard/SDCARD_D2: J11.1, R22.1
/jetson_sdcard/SDCARD_D3: J11.2, R25.1
/jetson_sdcard/SDCARD_PWR_EN: Q2.1, U3.H16
/jetson_sdcard/SDCARD_VDD: C24.1, C34.1, J11.4, U7.1
/jetson_usb/SS1_TX+: C37.2, U3.C43
/jetson_usb/SS1_TX-: C40.2, U3.C44
/jetson_usb/USB1_D+: D1.1, J7.3, U3.A38
/jetson_usb/USB1_D-: D1.2, J7.2, U3.A39
/jetson_usb/USB1_EN: R1.1, U3.A18, U10.4
/jetson_usb/USB1_VBUS: C11.1, FB1.2, J7.1
/power/DROP_DETECT: C102.1, D11.1, Q7.1, R48.2, R49.1
/power/RTN: C54.1, R38.2, R39.1, R40.2, U2.8, U2.17
/power/VIN: C53.1, J4.1, R36.1, U2.1, U2.2
/power/~PWR_EN: D11.2, Q8.3, R51.2, R52.1
CONSOLE_RX_1V8: U3.G12, U5.5
CONSOLE_RX_3V3: J5.4, R27.2, U5.19
CONSOLE_TX_1V8: U3.H12, U4.6
CONSOLE_TX_3V3: J5.16, U4.18
DISCHARGE: D11.3, J2.44, Q3.1, Q10.1, Q11.1, R53.1
FPGA_CONFIG_DATA0: J2.30, U3.F13
FPGA_CONFIG_DCLK: J2.32, U3.G13
FPGA_CONF_DONE: J2.28, U3.B19
FPGA_NCONFIG: J2.24, U3.B22
FPGA_NSTATUS: J2.26, U3.B21
GND: C1.2, C8.2, C9.2, C10.2, C11.2, C14.2, C15.2, C16.2, C17.2, C18.2, C19.2, C20.2, C21.2, C22.1, C23.2, C24.2, C33.2, C34.2, C35.1, C36.2, C38.2, C41.2, C42.2, C43.2, C44.2, C45.2, C47.2, C48.2, C49.2, C50.2, C51.2, C52.2, C53.2, C55.2, C56.2, C57.2, C58.1, C59.1, C78.1, C91.2, C92.2, C93.2, C94.2, C96.2, C97.2, C98.2, C99.2, C101.2, C102.2, C103.2, C104.2, C105.2, C106.2, C107.2, C162.2, D1.3, D2.3, D3.3, D4.3, D5.3, D6.3, D7.2, D8.1, J1.4, J1.10, J2.1, J2.7, J2.13, J2.19, J2.22, J2.25, J2.31, J2.34, J2.37, J2.43, J2.46, J2.49, J2.51, J2.52, J2.53, J2.54, J2.55, J2.56, J3.5, J3.6, J4.2, J5.1, J5.10, J5.11, J5.12, J5.20, J6.2, J6.5, J6.8, J6.11, J6.17, J6.20, J7.4, J7.7, J7.13, J7.16, J8.1, J11.6, J11.10, J11.11, Q1.2, Q2.2, Q3.2, Q4.2, Q7.2, Q8.2, Q10.2, Q11.2, R29.1, R30.1, R31.1, R32.1, R46.2, R47.2, R49.2, R50.2, R52.2, R53.2, SW1.2, SW2.2, SW3.2, U1.12, U1.13, U1.14, U2.9, U3.A3, U3.A4, U3.A28, U3.A37, U3.A40, U3.A43, U3.B3, U3.B4, U3.B14, U3.B31, U3.B38, U3.B41, U3.B44, U3.B47, U3.C3, U3.C4, U3.C21, U3.C24, U3.C27, U3.C30, U3.C33, U3.C36, U3.C39, U3.C42, U3.C45, U3.D20, U3.D23, U3.D26, U3.D29, U3.D32, U3.D35, U3.D38, U3.D41, U3.D44, U3.E19, U3.E22, U3.E25, U3.E28, U3.E31, U3.E34, U3.E37, U3.E40, U3.E43, U3.E46, U3.F10, U3.F15, U3.F20, U3.F21, U3.F24, U3.F27, U3.F30, U3.F33, U3.F36, U3.F39, U3.F42, U3.F45, U3.F49, U3.G3, U3.G17, U3.G20, U3.G23, U3.G26, U3.G29, U3.G32, U3.G35, U3.G38, U3.G41, U3.G44, U3.G45, U3.G46, U3.G47, U3.G50, U3.H19, U3.H22, U3.H25, U3.H28, U3.H31, U3.H34, U3.H37, U3.H40, U3.H41, U3.H42, U3.H43, U3.H46, U3.H49, U4.11, U4.12, U4.13, U4.22, U5.2, U5.11, U5.12, U5.13, U5.22, U6.2, U7.2, U8.33, U9.11, U10.2, U11.2, U12.2, U13.2, U14.12, U14.13, U14.14
GPIO0_1V8: U3.G8, U9.1
GPIO0_3V3: J1.1, U9.20
GPIO1_1V8: U3.F14, U5.7
GPIO1_3V3: J5.6, R29.2, U5.17
GPIO2_1V8: U3.C20, U5.8
GPIO2_3V3: J5.7, R30.2, U5.16
GPIO3_1V8: U3.A23, U5.10
GPIO3_3V3: J5.9, R32.2, U5.14
GPIO4_1V8: U3.A22, U5.9
GPIO4_3V3: J5.8, R31.2, U5.15
GPIO5_1V8: U3.A24, U4.10
GPIO5_3V3: J5.19, U4.14
GPIO6_1V8: U3.B26, U4.8
GPIO6_3V3: J5.18, U4.16
GPIO7_1V8: U3.B28, U4.9
GPIO7_3V3: J5.17, U4.15
HDMI_PULLDOWNS: Q1.1, R11.2
I2C0_SCL_1V8: U3.E15, U9.4
I2C0_SCL_3V3: J1.6, U9.17
I2C0_SDA_1V8: U3.D15, U9.3
I2C0_SDA_3V3: J1.3, U9.18
IMU_RX1_1V8: U3.D9, U4.3
IMU_RX1_3V3: J2.16, U4.21
IMU_TX1_1V8: U3.D10, U5.4
IMU_TX1_3V3: J2.14, R10.2, U5.20
JETSON_CARRIER_PWR_ON: J2.8, Q8.1, U1.17, U3.A48, U14.17
JETSON_PWR_BAD: Q7.3, U2.14, U3.B8
JETSON_RESET_OUT: J2.10, U3.A46
JETSON_VDD_MOD: C94.1, C96.1, C97.1, C98.1, C99.1, FB19.1, FB20.1, FB21.1, U3.A1, U3.A2, U3.B1, U3.B2, U3.C1, U3.C2
LED: J2.36, R44.2, U4.20
LED_1V8: U3.H7, U4.4
unnamed: C9.1, C10.1, FB1.1, U10.1
unnamed: C23.1, U18.SHLD
unnamed: C38.1, R34.1
unnamed: C39.2, R4.2, R5.1, U14.1
unnamed: C43.1, J6.18, U8.13
unnamed: C45.1, R35.1
unnamed: C46.2, R2.2, R3.1, U1.1
unnamed: C49.1, C50.1, FB12.1, U11.1
unnamed: C54.2, U2.12
unnamed: C78.2, U18.5, U18.6
unnamed: C101.1, D10.2, Q6.1, R47.1
unnamed: C103.1, C104.1, D10.1, Q6.2, R50.1
unnamed: C107.1, SW1.1, U3.E1
unnamed: D8.2, R44.1
unnamed: FB3.1, R12.2
unnamed: FB4.1, R13.2
unnamed: FB5.1, R14.2
unnamed: FB6.1, R15.2
unnamed: FB7.1, R16.2
unnamed: FB8.1, R17.2
unnamed: FB9.1, R18.2
unnamed: FB10.1, R19.2
unnamed: FB3.2, FB4.2, FB5.2, FB6.2, FB7.2, FB8.2, FB9.2, FB10.2, Q1.3
unnamed: J8.4, R42.1
unnamed: Q2.3, R26.2, U7.4
unnamed: Q3.3, R6.2
unnamed: Q4.3, R42.2
unnamed: Q6.3, R48.1
unnamed: Q10.3, R55.2
unnamed: Q11.3, R56.2
unnamed: R1.2, U10.3
unnamed: R3.2, U1.3
unnamed: R5.2, U14.3
unnamed: R7.2, U3.E47
unnamed: R8.2, U3.F46
unnamed: R20.2, U3.G18
unnamed: R21.2, U3.H18
unnamed: R22.2, U3.F19
unnamed: R23.2, U3.G19
unnamed: R24.2, U3.H17
unnamed: R25.2, U3.F18
unnamed: R33.2, U11.3
unnamed: R34.2, U14.4, U14.5, U14.6
unnamed: R35.2, U1.4, U1.5, U1.6
unnamed: R36.2, R37.1, U2.3
unnamed: R37.2, R38.1, U2.5
unnamed: R39.2, U2.6
unnamed: R40.1, U2.11
PCIE_LANE0_RX+: J2.45, U3.H44
PCIE_LANE0_RX-: J2.47, U3.H45
PCIE_LANE0_TX+: C6.1, J2.39
PCIE_LANE0_TX-: C2.1, J2.41
PCIE_LANE1_RX+: J2.33, U3.G42
PCIE_LANE1_RX-: J2.35, U3.G43
PCIE_LANE1_TX+: C7.1, J2.27
PCIE_LANE1_TX-: C3.1, J2.29
PCIE_LANE2_RX+: J2.23, U3.F40
PCIE_LANE2_RX-: J2.21, U3.F41
PCIE_LANE2_TX+: C12.1, J2.17
PCIE_LANE2_TX-: C4.1, J2.15
PCIE_LANE3_RX+: J2.9, U3.G39
PCIE_LANE3_RX-: J2.11, U3.G40
PCIE_LANE3_TX+: C13.1, J2.5
PCIE_LANE3_TX-: C5.1, J2.3
PCIE_REFCLK+: J2.48, U3.A44
PCIE_REFCLK-: J2.50, U3.A45
PCIE_RST_3V3: J2.42, U3.C49
SPI0_CLK_1V8: U3.E3, U9.8
SPI0_CLK_3V3: J1.9, U9.13
SPI0_CS_1V8: U3.F3, U9.6
SPI0_CS_3V3: J1.8, U9.15
SPI0_MISO_1V8: U3.E4, U9.7
SPI0_MISO_3V3: J1.7, U9.14
SPI0_MOSI_1V8: U3.F4, U9.5
SPI0_MOSI_3V3: J1.5, U9.16
UART2_RX_1V8: U3.B15, U5.3
UART2_RX_3V3: J5.3, R9.2, U5.21
UART2_TX_1V8: U3.B16, U4.7
UART2_TX_3V3: J5.15, U4.17
UART3_RX_1V8: U3.H9, U5.6
UART3_RX_3V3: J5.5, R28.2, U5.18
UART3_TX_1V8: U3.H10, U4.5
UART3_TX_3V3: J5.13, U4.19
USB0_D+: D5.1, J3.3, U3.B39
USB0_D-: D5.2, J3.2, U3.B40
USB0_ID: D6.2, J3.4, U3.A36
USB0_VBUS: J3.1, U3.B37
USB1_SSRX+: D4.1, J7.15, U3.F43
USB1_SSRX-: D4.2, J7.14, U3.F44
USB1_SSTX+: C37.1, D3.1, J7.18
USB1_SSTX-: C40.1, D3.2, J7.17
USB2_5V_LIM: C51.1, FB12.2, J7.10
USB2_D+: D2.2, J7.12, U3.B42
USB2_D-: D2.1, J7.11, U3.B43

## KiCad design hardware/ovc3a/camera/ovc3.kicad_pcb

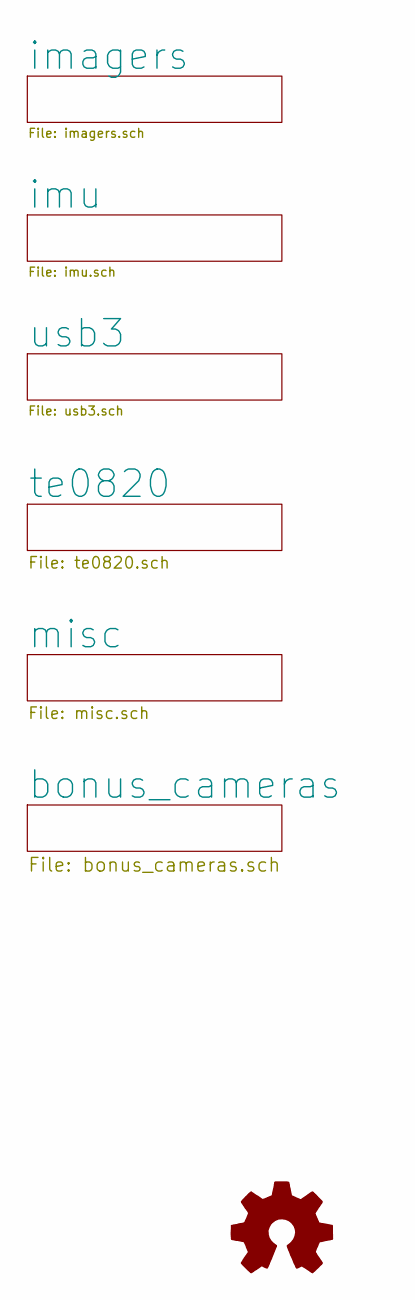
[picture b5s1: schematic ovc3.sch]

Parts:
LOGO1: Logo_Open_Hardware_Small; OSHW-Symbol_6.7x6mm_SilkScreen; MPN DNP
